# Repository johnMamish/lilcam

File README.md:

This is a USB camera which uses the ultra-low-power Himax HM01B0 and HM0360 sensors. It's intended to act as an evaluation platform for these sensors; commercially available evaluation platforms don't allow for the use of custom optics.

Please contact me if you're interested in buying one, we might be able to set something up.

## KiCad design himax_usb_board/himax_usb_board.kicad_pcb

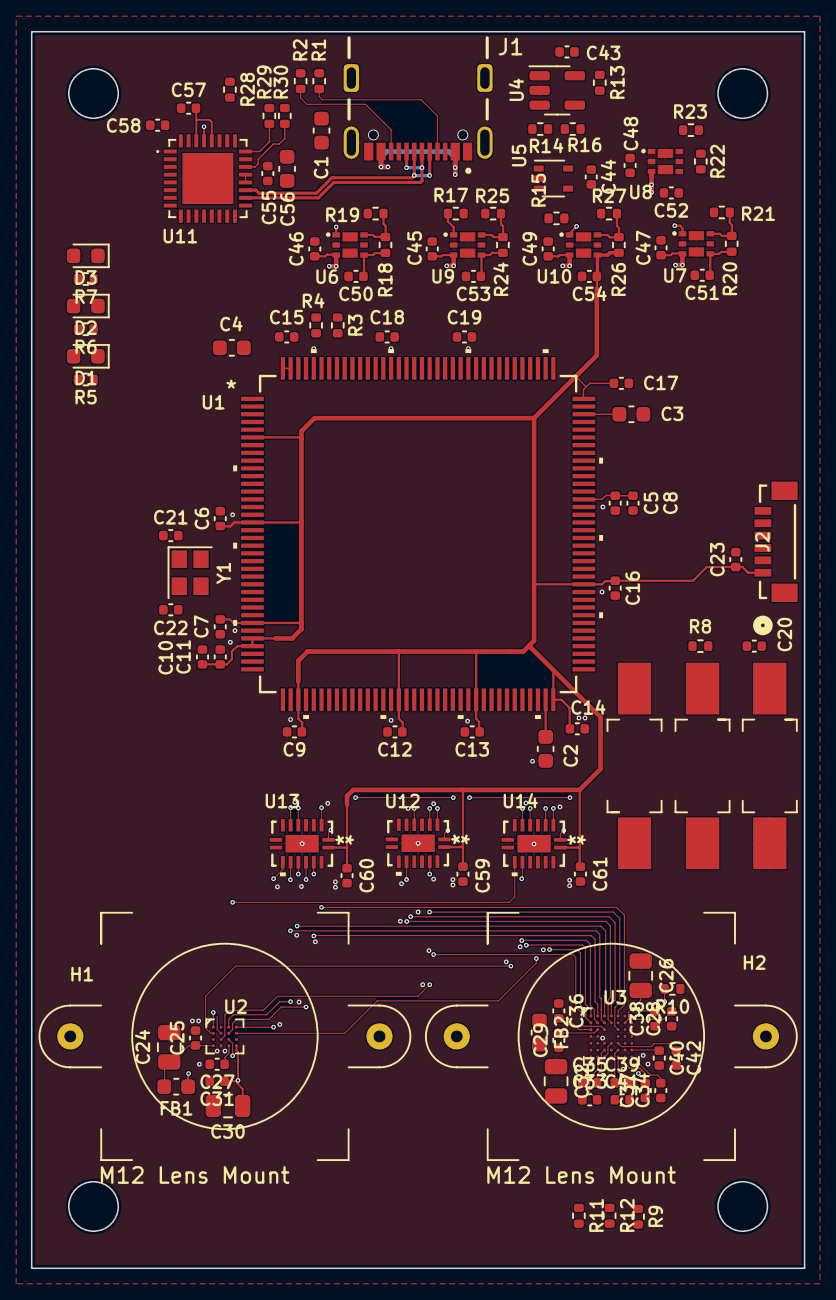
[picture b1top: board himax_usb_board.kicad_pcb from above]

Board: 4 copper layers, 50.0 x 80.0 mm, 118 parts (0 on the bottom side), 87 nets.

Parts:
C1, C4: 4.7u; C_0603_1608Metric
C2, C3, C56: 2.2u; C_0603_1608Metric
C5, C6, C7, C9, C10, C12, C13, C14, C15, C16, C17, C18, C19, C20, C23, C25, C27, C28, C29, C31, C33, C34, C35, C36, C37, C38, C39, C40, C41, C42, C55, C57, C58, C59, C60, C61: 100n; C_0402_1005Metric
C8, C11, C43, C44, C45, C46, C47, C48, C49, C50, C51, C52, C53, C54: 1u; C_0402_1005Metric
C21, C22: C_Small; C_0402_1005Metric
C24, C26, C30, C32: 10u; C_0805_2012Metric
D1, D2, D3: LED; LED_0603_1608Metric
FB1, FB2: FerriteBead_Small; C_0603_1608Metric
H1, H2: m12_lens_mount_mech
J1: USB4105GFA; GCT_USB4105GFA
J2: BM06B-SURS-TF_SWD; CONN6x1_BM06B-SURS-TF_JST
R1, R2, R9, R11, R12, R30: 5.1k; R_0402_1005Metric
R3, R4, R13, R14, R15, R16, R17, R28: 10k; R_0402_1005Metric
R5, R6, R7, R8: R_Small_US; R_0402_1005Metric
R10: 0; R_0402_1005Metric
R18: 5.6k; R_0402_1005Metric
R19: 1.6k; R_0402_1005Metric
R20: 3.3k; R_0402_1005Metric
R21, R23: 1.2k; R_0402_1005Metric
R22: 2.4k; R_0402_1005Metric
R24: 16k; R_0402_1005Metric
R25: 2.2k; R_0402_1005Metric
R26: 12k; R_0402_1005Metric
R27: 2k; R_0402_1005Metric
R29: 12k 1%; R_0402_1005Metric
SW1, SW2, SW3: SW_Push; TL3302AFxxxQG
U1: STM32F750Z8T6; LQFP-144_STM
U2: hm01b0-mwa; hm01b0-xWA
U3: HM0360; hm0360
U4: TL331; SOT-23-5
U5: 74AHC1G08; SOT-353_SC-70-5
U6, U7, U8, U9, U10: AP7331-SNG-7; DFN200X200X60-8N
U11: USB3320C-EZK-TR; QFN50P500X500X100-33N330X330
U12, U13, U14: 74CBTLV3257BQ_115; DHVQFN16_SOT763-1_NEX
Y1: 12MHz; Crystal_SMD_2520-4Pin_2.5x2.0mm

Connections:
+1V2: C52.1, R10.1, R22.1, U8.4 (OUT)
+1V5: C27.1, C51.1, R20.1, U2.D3 (DVDD), U7.4 (OUT)
+1V8: C50.1, C57.2, R18.1, U6.4 (OUT), U11.28 (VDD18), U11.30 (VDD18__1)
+2V8: C4.1, C6.1, C7.1, C9.1, C10.1, C11.1, C12.1, C13.1, C14.1, C15.1, C16.1, C17.1, C18.1, C19.1, C23.1, C26.2, C28.2, C29.2, C30.1, C31.1, C54.1, C58.2, C59.2, C60.2, C61.2, FB1.1, FB2.1, J2.1, R3.1, R4.1, R26.1, R28.1, SW2.2, U1.6 (VBAT), U1.17 (VDD), U1.30 (VDD), U1.32 (VREF+), U1.33 (VDDA), U1.39 (VDD), U1.52 (VDD), U1.62 (VDD), U1.72 (VDD), U1.84 (VDD), U1.108 (VDD), U1.121 (VDD), U1.131 (VDD), U1.143 (PDR_ON), U1.144 (VDD), U2.D4 (IOVDD), U3.B6 (IOVDD), U3.C2 (IOVDD), U3.E4 (I2C_SEL1), U3.G3 (I2C_SEL0), U4.1 (-), U10.4 (OUT), U11.8 (REFSEL0), U11.14 (REFSEL2), U11.32 (VDDIO), U12.16 (VCC), U13.16 (VCC), U14.16 (VCC)
+3V3: C5.1, C8.1, C53.1, C55.2, C56.2, R24.1, U1.95 (VDDUSB), U9.4 (OUT), U11.20 (VDD33), U11.21 (VBAT)
/bus mux/camera_data.d0: U1.96 (PC6), U14.4 (1A)
/bus mux/camera_data.d1: U1.97 (PC7), U13.12 (4A)
/bus mux/camera_data.d2: U1.98 (PC8), U13.9 (3A)
/bus mux/camera_data.d3: U1.99 (PC9), U13.7 (2A)
/bus mux/camera_data.d4: U1.3 (PE4), U12.9 (3A)
/bus mux/camera_data.d5: U1.117 (PD3), U12.7 (2A)
/bus mux/camera_data.d6: U1.4 (PE5), U12.12 (4A)
/bus mux/camera_data.d7: U1.5 (PE6), U13.4 (1A)
/bus mux/camera_data.hsync: U1.40 (PA4), U14.7 (2A)
/bus mux/camera_data.pclk: U1.36 (PA2), U14.9 (3A)
/bus mux/camera_data.vsync: U1.124 (PG9), U12.4 (1A)
/bus mux/camera_select: U1.127 (PG12), U12.1 (S), U13.1 (S), U14.1 (S)
/bus mux/hm01b0_data.d0: U2.B4 (D0), U14.3 (1B2)
/bus mux/hm01b0_data.d1: U2.B3 (D1), U13.13 (4B2)
/bus mux/hm01b0_data.d2: U2.A4 (D2), U13.10 (3B2)
/bus mux/hm01b0_data.d3: U2.A3 (D3), U13.6 (2B2)
/bus mux/hm01b0_data.hsync: U2.B1 (LVLD), U14.6 (2B2)
/bus mux/hm01b0_data.pclk: U2.C3 (PCLK0), U14.10 (3B2)
/bus mux/hm01b0_data.vsync: U2.C2 (FVLD), U12.3 (1B2)
/bus mux/hm0360_data.d0: U3.B1 (D0), U14.2 (1B1)
/bus mux/hm0360_data.d1: U3.A2 (D1), U13.14 (4B1)
/bus mux/hm0360_data.d2: U3.B3 (D2), U13.11 (3B1)
/bus mux/hm0360_data.d3: U3.A3 (D3), U13.5 (2B1)
/bus mux/hm0360_data.d4: U3.B4 (D4), U12.11 (3B1)
/bus mux/hm0360_data.d5: U3.A4 (D5), U12.5 (2B1)
/bus mux/hm0360_data.d6: U3.C5 (D6), U12.14 (4B1)
/bus mux/hm0360_data.d7: U3.A5 (D7), U13.2 (1B1)
/bus mux/hm0360_data.hsync: U3.A1 (HVLD), U14.5 (2B1)
/bus mux/hm0360_data.pclk: U3.B2 (PCLK0), U14.11 (3B1)
/bus mux/hm0360_data.vsync: U3.C3 (FVLD), U12.2 (1B1)
/image sensors/cameras_i2c.scl: R4.2, U1.139 (PB8), U2.B2 (SCL), U3.E6 (SCL)
/image sensors/cameras_i2c.sda: R3.2, U1.137 (PB7), U2.A1 (SDA), U3.E7 (SDA)
/image sensors/hm0360_cfg.clksel: R11.1, U3.B5 (CLK_SEL)
/image sensors/hm0360_cfg.xshut: R9.1, U3.F4 (XSHUTDOWN)
/image sensors/hm0360_cfg.xsleep: R12.1, U3.G4 (XSLEEP)
/microcontroller/3v3_en: R15.1, U5.1
/microcontroller/swo: J2.5, U1.133 (PB3)
/microcontroller/ulpi.clk: U1.41 (PA5), U11.1 (CLKOUT)
/microcontroller/ulpi.d0: U1.37 (PA3), U11.3 (DATA0)
/microcontroller/ulpi.d1: U1.46 (PB0), U11.4 (DATA1)
/microcontroller/ulpi.d2: U1.47 (PB1), U11.5 (DATA2)
/microcontroller/ulpi.d3: U1.69 (PB10), U11.6 (DATA3)
/microcontroller/ulpi.d4: U1.70 (PB11), U11.7 (DATA4)
/microcontroller/ulpi.d5: U1.73 (PB12), U11.9 (DATA5)
/microcontroller/ulpi.d6: U1.74 (PB13), U11.10 (DATA6)
/microcontroller/ulpi.d7: U1.135 (PB5), U11.13 (DATA7)
/microcontroller/ulpi.dir: U1.28 (PC2), U11.31 (DIR)
/microcontroller/ulpi.nxt: U1.29 (PC3), U11.2 (NXT)
/microcontroller/ulpi.stp: U1.26 (PC0), U11.29 (STP)
/microcontroller/~rst: C20.1, J2.6, SW3.1, U1.25 (NRST)
/ulpi/usb.d+: J1.A6 (DP1), J1.B6 (DP2), U11.18 (DP)
/ulpi/usb.d-: J1.A7 (DN1), J1.B7 (DN2), U11.19 (DM)
GND: C1.2, C2.2, C3.2, C4.2, C5.2, C6.2, C7.2, C8.2, C9.2, C10.2, C11.2, C12.2, C13.2, C14.2, C15.2, C16.2, C17.2, C18.2, C19.2, C20.2, C21.1, C22.1, C23.2, C24.2, C25.2, C26.1, C27.2, C28.1, C29.1, C30.2, C31.2, C32.1, C33.1, C34.1, C35.1, C36.1, C37.1, C38.1, C39.2, C40.2, C41.2, C42.2, C43.2, C44.2, C45.2, C46.2, C47.2, C48.2, C49.2, C50.2, C51.2, C52.2, C53.2, C54.2, C55.1, C56.1, C57.1, C58.1, C59.1, C60.1, C61.1, D1.1 (K), D2.1 (K), D3.1 (K), J1.A1_B12 (GND), J1.B1_A12 (GND__1), J1.SH1 (SHELL_GND), J1.SH2 (SHELL_GND__1), J1.SH3 (SHELL_GND__2), J1.SH4 (SHELL_GND__3), J2.3, R1.1, R2.1, R8.2, R9.2, R11.2, R12.2, R14.2, R15.2, R17.2, R19.2, R21.2, R23.2, R25.2, R27.2, R29.2, SW3.2, U1.16 (VSS), U1.31 (VSSA), U1.38 (VSS), U1.51 (VSS), U1.61 (VSS), U1.83 (VSS), U1.94 (VSS), U1.107 (VSS), U1.120 (VSS), U1.130 (VSS), U2.D2 (GND), U3.B7 (DGND), U3.D1 (DGND), U3.D2 (RTC), U3.E3 (AGND), U3.F6 (DGND), U4.2 (V-), U5.3 (GND), U6.2 (GND), U6.7 (GNDPAD1), U6.8 (GNDPAD2), U7.2 (GND), U7.7 (GNDPAD1), U7.8 (GNDPAD2), U8.2 (GND), U8.7 (GNDPAD1), U8.8 (GNDPAD2), U9.2 (GND), U9.7 (GNDPAD1), U9.8 (GNDPAD2), U10.2 (GND), U10.7 (GNDPAD1), U10.8 (GNDPAD2), U11.11 (REFSEL1), U11.33 (EXP), U12.6 (2B2), U12.8 (GND), U12.10 (3B2), U12.13 (4B2), U12.15 (*OE), U12.17 (GND), U13.3 (1B2), U13.8 (GND), U13.15 (*OE), U13.17 (GND), U14.8 (GND), U14.13 (4B2), U14.14 (4B1), U14.15 (*OE), U14.17 (GND)
unnamed: C2.1, U1.71 (VCAP_1)
unnamed: C3.1, U1.106 (VCAP_2)
unnamed: C21.2, U1.23 (PH0), Y1.1
unnamed: C22.2, U1.24 (PH1), Y1.2
unnamed: C24.1, C25.1, FB1.2, U2.D1 (AVDD)
unnamed: C32.2, C33.2, C34.2, FB2.2, U3.G2 (AVDD), U3.G7 (AVDD)
unnamed: C35.2, C36.2, C37.2, C38.2, R10.2, U3.A7 (DVDD), U3.C1 (DVDD), U3.F3 (DVDD), U3.G6 (DVDD)
unnamed: C39.1, U3.F5 (HVP)
unnamed: C40.1, U3.F7 (VREF3)
unnamed: C41.1, U3.G5 (VREF2)
unnamed: C42.1, U3.E5 (VREF1)
unnamed: D1.2 (A), R5.2
unnamed: D2.2 (A), R6.2
unnamed: D3.2 (A), R7.2
unnamed: J1.A5 (CC1), R1.2
unnamed: J1.B5 (CC2), R2.2
unnamed: R8.1, SW2.1, U1.138 (BOOT0)
unnamed: R13.2, R14.1, U4.3 (+)
unnamed: R16.1, U4.4, U5.2
unnamed: R17.1, U5.4, U9.1 (EN)
unnamed: R18.2, R19.1, U6.6 (ADJ)
unnamed: R20.2, R21.1, U7.6 (ADJ)
unnamed: R22.2, R23.1, U8.6 (ADJ)
unnamed: R24.2, R25.1, U9.6 (ADJ)
unnamed: R26.2, R27.1, U10.6 (ADJ)
unnamed: R28.2, U11.27 (~RESETB)
unnamed: R29.1, U11.24 (RBIAS)
unnamed: R30.1, U11.22 (VBUS)
VCC: C1.1, C43.1, C44.1, C45.1, C46.1, C47.1, C48.1, C49.1, J1.A4_B9 (VBUS), J1.B4_A9 (VBUS__1), R13.1, R16.2, R30.2, U4.5 (V+), U5.5 (VCC), U6.1 (EN), U6.3 (IN), U7.1 (EN), U7.3 (IN), U8.1 (EN), U8.3 (IN), U9.3 (IN), U10.1 (EN), U10.3 (IN)

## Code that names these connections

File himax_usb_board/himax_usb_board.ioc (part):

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Mcu.Name=STM32F750Z8Tx
Mcu.Package=LQFP144
Mcu.UserName=STM32F750Z8Tx
PA10.Signal=GPIO_Output
PA13.Mode=Serial_Wire
PA13.Signal=SYS_JTMS-SWDIO
PA14.Mode=Serial_Wire
PA14.Signal=SYS_JTCK-SWCLK
PA2.Signal=S_TIM2_CH3
PA3.Mode=Device_HS
PA3.Signal=USB_OTG_HS_ULPI_D0
PA4.Mode=Slave_8_bits_External_Synchro
PA4.Signal=DCMI_HSYNC
PA5.Mode=Device_HS
PA5.Signal=USB_OTG_HS_ULPI_CK
PA6.Mode=Slave_8_bits_External_Synchro
PA6.Signal=DCMI_PIXCLK
PB0.Mode=Device_HS
PB0.Signal=USB_OTG_HS_ULPI_D1
PB1.Mode=Device_HS
PB1.Signal=USB_OTG_HS_ULPI_D2
PB10.Mode=Device_HS
PB10.Signal=USB_OTG_HS_ULPI_D3
PB11.Mode=Device_HS
PB11.Signal=USB_OTG_HS_ULPI_D4
PB12.Mode=Device_HS
PB12.Signal=USB_OTG_HS_ULPI_D5
PB13.Mode=Device_HS
PB13.Signal=USB_OTG_HS_ULPI_D6
PB5.Mode=Device_HS
PB5.Signal=USB_OTG_HS_ULPI_D7
PB6.Signal=S_TIM4_CH1
PB7.Mode=I2C
PB7.Signal=I2C1_SDA
PB8.Mode=I2C
PB8.Signal=I2C1_SCL
PC0.Mode=Device_HS
PC0.Signal=USB_OTG_HS_ULPI_STP
PC2.Mode=Device_HS
PC2.Signal=USB_OTG_HS_ULPI_DIR
PC3.Mode=Device_HS
PC3.Signal=USB_OTG_HS_ULPI_NXT
PC6.Mode=Slave_8_bits_External_Synchro
PC6.Signal=DCMI_D0
PC7.Mode=Slave_8_bits_External_Synchro
PC7.Signal=DCMI_D1
PC8.Mode=Slave_8_bits_External_Synchro
PC8.Signal=DCMI_D2
PC9.Mode=Slave_8_bits_External_Synchro
PC9.Signal=DCMI_D3
PD3.Mode=Slave_8_bits_External_Synchro
PD3.Signal=DCMI_D5
PE11.Signal=S_TIM1_CH2
PE13.Signal=S_TIM1_CH3
PE14.Signal=S_TIM1_CH4
PE15.GPIOParameters=GPIO_Label
PE15.GPIO_Label=camera_select
PE15.Signal=GPIO_Output
PE4.Mode=Slave_8_bits_External_Synchro
PE4.Signal=DCMI_D4
PE5.Mode=Slave_8_bits_External_Synchro
PE5.Signal=DCMI_D6
PE6.Mode=Slave_8_bits_External_Synchro
PE6.Signal=DCMI_D7
PG9.Mode=Slave_8_bits_External_Synchro
PG9.Signal=DCMI_VSYNC
PH0/OSC_IN.Mode=HSE-External-Oscillator
PH0/OSC_IN.Signal=RCC_OSC_IN
PH1/OSC_OUT.Mode=HSE-External-Oscillator
PH1/OSC_OUT.Signal=RCC_OSC_OUT
RCC.HSE_VALUE=12000000
RCC.SYSCLKFreq_VALUE=216000000
RCC.SYSCLKSource=RCC_SYSCLKSOURCE_PLLCLK
board=custom

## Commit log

2023-11-01 schematic wip
2023-11-10 board routing wip
2024-01-09 hardware wip
2024-01-09 change dir structure
2024-01-09 rename some files
2024-01-09 remove some extra ioc files
2024-01-09 add gpio names to ioc file
2024-01-12 update some hardware design files
2024-01-12 firmware connects over USB and appears to read camera frames
2024-01-22 add some util scripts
2024-01-22 rename some stuff
2024-01-23 add wip DFU bootloader
2024-01-24 video streaming over USB CDC passes smoke test!
2024-01-24 bootloader works!
2024-01-25 fix startup bug; was due to gated pixclk on image sensor
2024-01-25 add revision list for potential hardware revision
2024-01-30 camera wip; add exti9 interrupt for trigger in
2024-02-01 firmware triggering wip
2024-02-22 triggered hm01b0 reads wip
2024-03-12 some bootloader stuff updated
2024-03-12 camera updates at runtime wip
2024-03-12 runtime camera updates pass smoke test
2024-03-12 fix race condition in camera_read_task; runtime camera config update appears to work.
2024-03-15 hm0360 passes smoke test
2024-04-15 tusb integraiton wip
2024-04-17 autoexposure disable wip
2024-04-22 add nanopb
2024-04-22 update serialcam to use new camera command interface; serialcam.py must enable DCMI to start video.
2024-05-03 camera python script update WIP
2024-05-03 fix numpy dimensioning error in camera interface
2024-05-03 make preamble detection stricter
2024-05-03 add numpy file saving
2024-05-16 fix DMA reset bug
2024-05-24 uart7 now outputs cprintf on PF7
2024-05-31 fix frame alignment bug
2024-05-31 remove bootloader space
